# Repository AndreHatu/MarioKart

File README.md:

# Mario Kart with RC cars and ESP32s
This project aims at developing a real-life Mario Kart with RC cars and ESP32s.
The boards used utilize a single-core MCU (ESP-MINI-1 and ESP-SOLO-1). 
Schematics and wiring will be posted in the near future.

ECE477 Senior Design at Purdue University.

## How it works
We control RC cars with electronics replaced by our own ESP32. All communications are made using ESP-NOW, which is a Wi-Fi like wireless communication protocol. It enables low latency and long distance transmission of packets, with the only restriction they must be less than 250 bytes long.
Then, we place checkpoint towers and power-up blocks along the desired track and when cars run over them, a NFC tag is read and its information is sent to a central tower, which either updates records of checkpoints or determines what modifier to give the cars. Modifiers are randomly chosen using ESP's ```esp_random()``` function. Checkpoints are stored in two-dimensional arrays initialized upon race creation.

## Cloning
When cloning this repo, make sure to use ```git clone --recursive git@github.com:AndreHatu/MarioKart.git``` or run ```git submodule update --init --recursive``` after doing a standard clone. 
This ensures all dependencies are downloaded.

## Config, Build and Flash
To build, you will need to have installed Espressif's idf from their website.
Then run the following commands from a terminal.

```
idf.py set-target esp32
idf.py menuconfig
```
Inside the menuconfig, you might need to set the ```Components->freeRTOS->Run only on first core``` option in case your ESP32 only has one core (like the ones we are using for the project)
Then you can build and flash with
```
idf.py build
idf.py -p (PORT) flash
```

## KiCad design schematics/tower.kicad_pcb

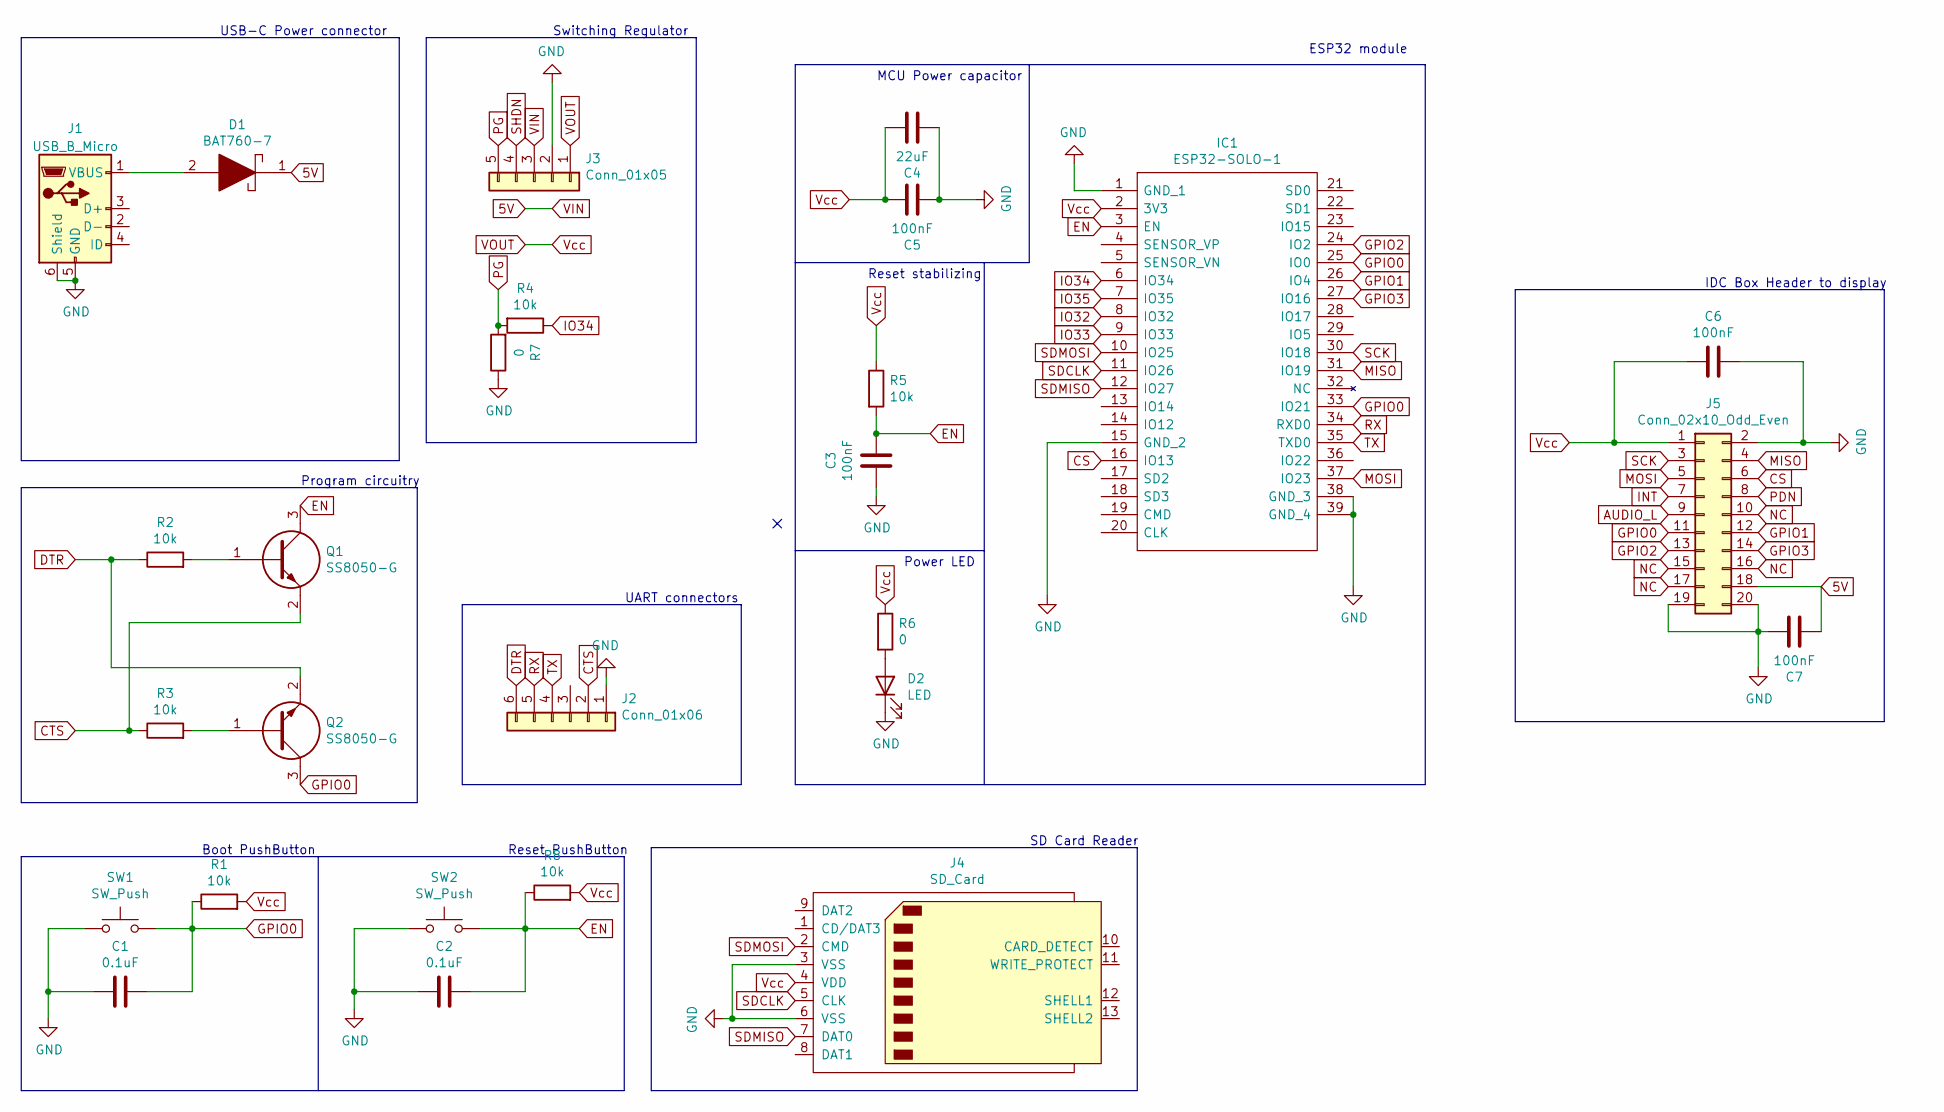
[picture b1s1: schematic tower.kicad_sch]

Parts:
C1, C2: 0.1uF; C_0805_2012Metric
C3, C5, C6, C7: 100nF; C_0805_2012Metric
C4: 22uF; C_0805_2012Metric
D1: BAT760-7; SOD2513X120N; Mouser Part Number 621-BAT760-7
D2: LED; APHCM2012QBCDF01
IC1: ESP32-SOLO-1; ESP32-WROOM-32; Manufacturer_Part_Number ESP32-SOLO-1; Mouser Part Number 356-ESP32-SOLO-1
J1: USB_B_Micro; USB_Micro-B_Molex-105017-0001
J2: Conn_01x06; PinSocket_1x06_P2.54mm_Vertical
J3: Conn_01x05; PinSocket_1x05_P2.54mm_Vertical
J4: SD_Card; SD_Kyocera_145638109211859+
J5: Conn_02x10_Odd_Even; PinSocket_2x10_P2.54mm_Vertical
Q1, Q2: SS8050-G; SOT95P240X115-3N; Mouser Part Number 750-SS8050-G
R1, R2, R3, R4, R5, R8: 10k; R_0805_2012Metric
R6, R7: 0; R_0805_2012Metric
SW1, SW2: SW_Push; SW_SPST_CK_KXT3

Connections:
5V: C7.2, D1.1, J3.3, J5.18
AUDIO_L: J5.9
CS: IC1.16 (IO13), J5.6
CTS: J2.2, Q1.2, R3.1
DTR: J2.6, Q2.2, R2.1
EN: C2.1, C3.1, IC1.3 (EN), Q1.3, R5.2, R8.1, SW2.2
GND: C1.2, C2.2, C3.2, C4.2, C5.2, C6.1, C7.1, D2.1 (K), IC1.1 (GND_1), IC1.15 (GND_2), IC1.38 (GND_3), IC1.39 (GND_4), J1.5 (GND), J1.6 (Shield), J2.1, J3.2, J4.3 (VSS), J4.6 (VSS), J5.2, J5.19, J5.20, R7.1, SW1.1, SW2.1
GPIO0: C1.1, IC1.25 (IO0), IC1.33 (IO21), J5.11, Q2.3, R1.1, SW1.2
GPIO1: IC1.26 (IO4), J5.12
GPIO2: IC1.24 (IO2), J5.13
GPIO3: IC1.27 (IO16), J5.14
INT: J5.7
IO32: IC1.8 (IO32)
IO33: IC1.9 (IO33)
IO34: IC1.6 (IO34), R4.1
IO35: IC1.7 (IO35)
MISO: IC1.31 (IO19), J5.4
MOSI: IC1.37 (IO23), J5.5
NC: J5.10, J5.15, J5.16, J5.17
unnamed: D2.2 (A), R6.2
unnamed: D1.2, J1.1 (VBUS)
unnamed: Q1.1, R2.2
unnamed: Q2.1, R3.2
PDN: J5.8
PG: J3.5, R4.2, R7.2
RX: IC1.34 (RXD0), J2.5
SCK: IC1.30 (IO18), J5.3
SDCLK: IC1.11 (IO26), J4.5 (CLK)
SDMISO: IC1.12 (IO27), J4.7 (DAT0)
SDMOSI: IC1.10 (IO25), J4.2 (CMD)
SHDN: J3.4
TX: IC1.35 (TXD0), J2.4
VOUT: C4.1, C5.1, C6.2, IC1.2 (3V3), J3.1, J4.4 (VDD), J5.1, R1.2, R5.1, R6.1, R8.2

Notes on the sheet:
Program circuitry
ESP32 module
IDC Box Header to display
Reset PushButton
Switching Regulator
SD Card Reader
Reset stabilizing
USB-C Power connector
UART connectors
Power LED
MCU Power capacitor
Boot PushButton

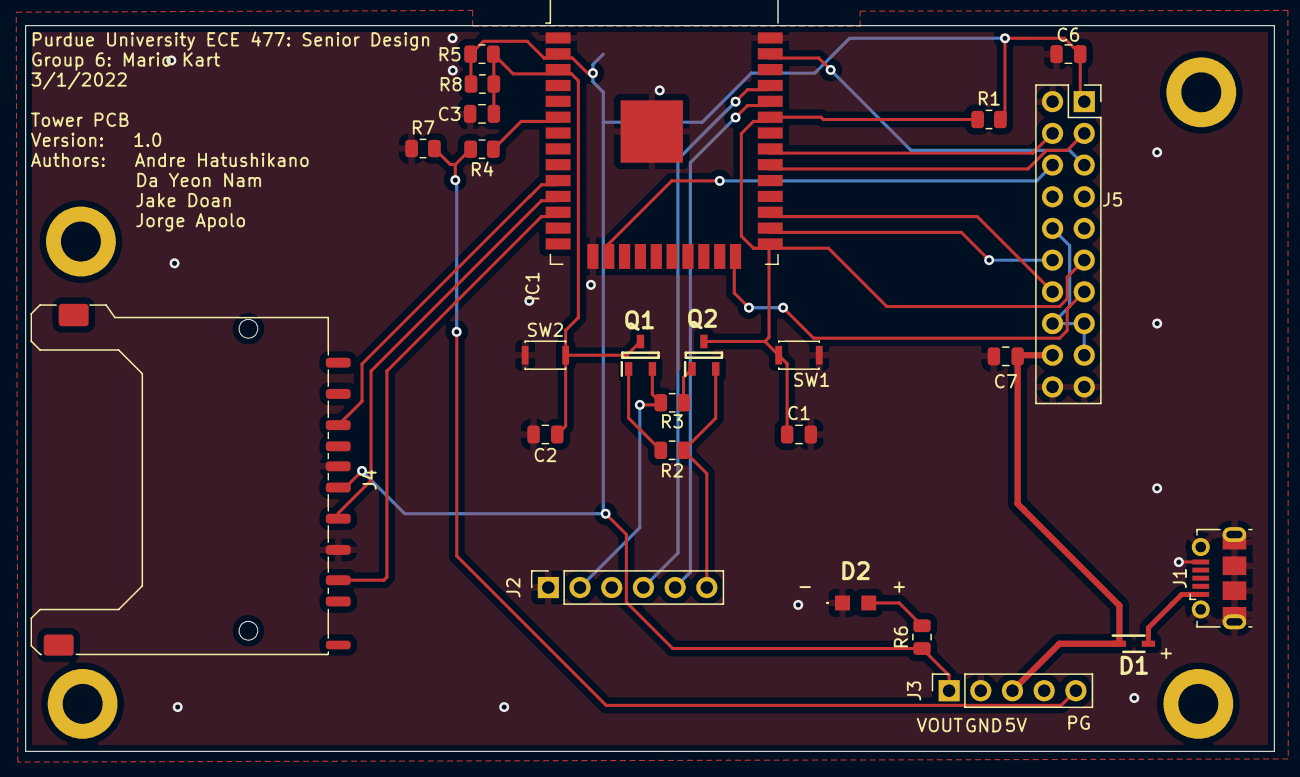
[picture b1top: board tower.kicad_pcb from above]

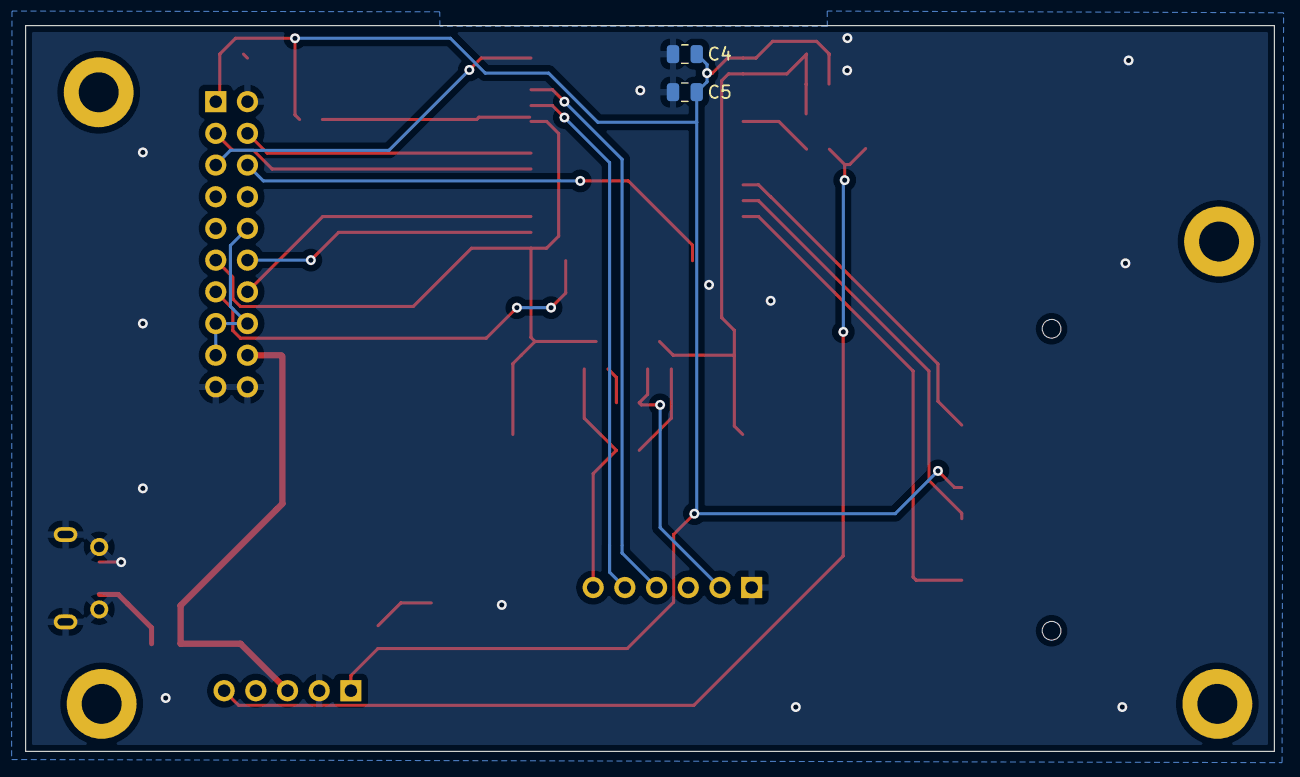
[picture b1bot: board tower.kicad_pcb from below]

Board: 2 copper layers, 100.1 x 58.2 mm, 27 parts (2 on the bottom side), 26 nets.

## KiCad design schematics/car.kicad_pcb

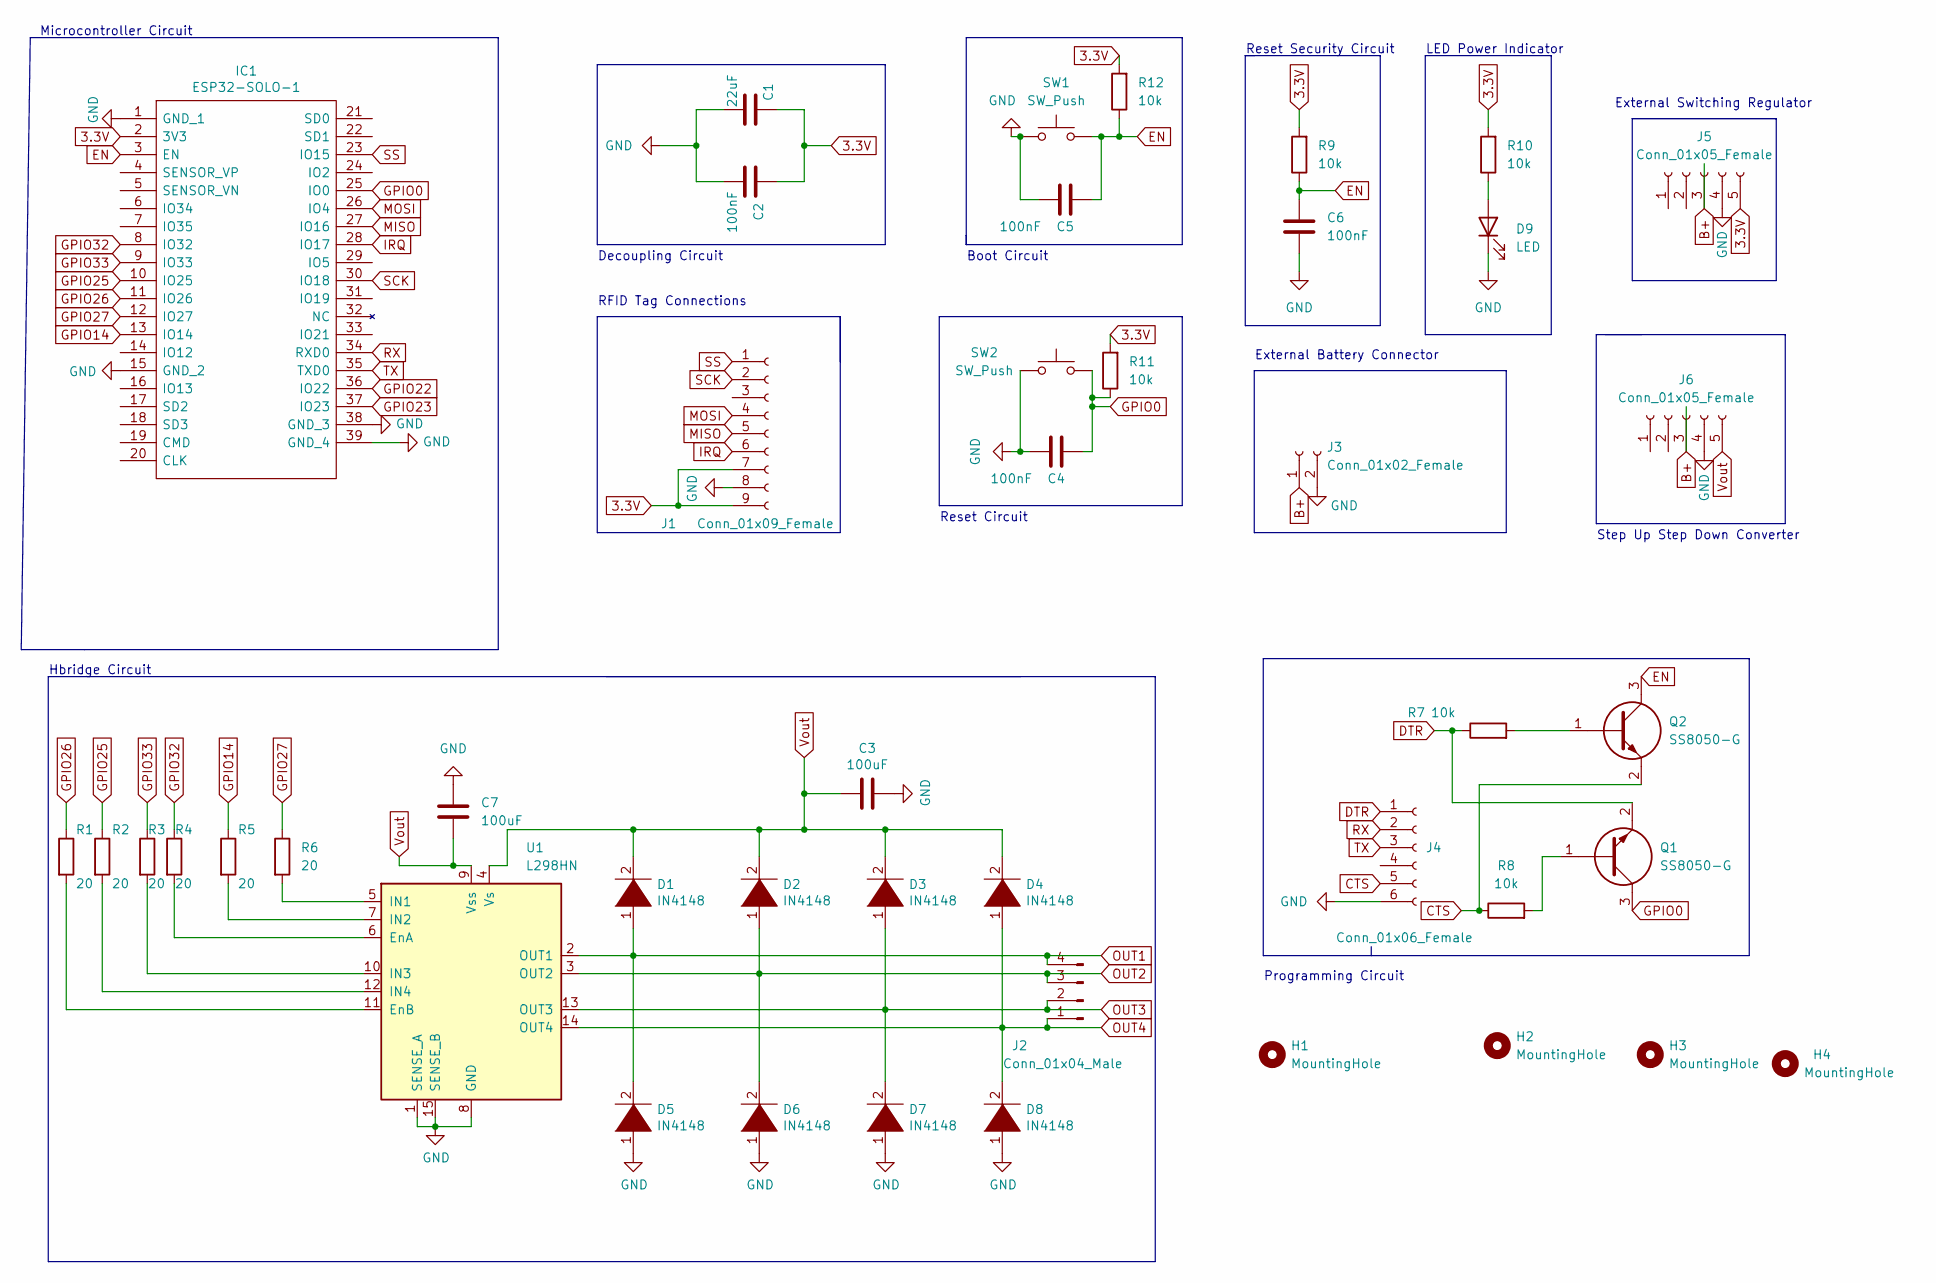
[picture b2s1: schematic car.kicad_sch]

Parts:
C1: 22uF; C_0805_2012Metric
C2, C4, C5, C6: 100nF; C_0805_2012Metric
C3, C7: 100uF; CP_Radial_D8.0mm_P5.00mm
D1, D2, D3, D4, D5, D6, D7, D8: IN4148; D_SOD-123F
D9: LED; APHCM2012QBCDF01
H1, H2, H3, H4: MountingHole; MountingHole_2.5mm_Pad
IC1: ESP32-SOLO-1; ESP32-SOLO-ONE; Manufacturer_Part_Number ESP32-SOLO-1; Mouser Part Number 356-ESP32-SOLO-1
J1: Conn_01x09_Female; PinHeader_1x09_P2.54mm_Vertical
J2: Conn_01x04_Male; PinHeader_1x04_P2.54mm_Vertical
J3: Conn_01x02_Female; PinHeader_1x02_P2.54mm_Vertical
J4: Conn_01x06_Female; PinHeader_1x06_P2.54mm_Vertical
J5, J6: Conn_01x05_Female; PinHeader_1x05_P2.54mm_Vertical
Q1, Q2: SS8050-G; SOT95P240X115-3N; Mouser Part Number 750-SS8050-G
R1, R2, R3, R4, R5, R6: 20; R_0805_2012Metric
R7, R8, R9, R10, R11, R12: 10k; R_0805_2012Metric
SW1, SW2: SW_Push; SW_SPST_CK_KXT3
U1: L298HN; TO-220-15_P2.54x2.54mm_StaggerOdd_Lead4.58mm_Vertical

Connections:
3.3V: C1.1, C2.1, IC1.2 (3V3), J1.7, J1.9, J5.5, R9.2, R10.2, R11.2, R12.2
B+: J3.1, J5.3, J6.3
CTS: J4.5, Q2.2, R8.1
DTR: J4.1, Q1.2, R7.1
EN: C5.2, C6.1, IC1.3 (EN), Q2.3, R9.1, R12.1, SW1.2
GND: C1.2, C2.2, C3.1, C4.1, C5.1, C6.2, C7.1, D5.1 (K), D6.1 (K), D7.1 (K), D8.1 (K), D9.1 (K), IC1.1 (GND_1), IC1.15 (GND_2), IC1.38 (GND_3), IC1.39 (GND_4), J1.8, J3.2, J4.6, J5.4, J6.4, SW1.1, SW2.1, U1.1 (SENSE_A), U1.8 (GND), U1.15 (SENSE_B)
GPIO0: C4.2, IC1.25 (IO0), Q1.3, R11.1, SW2.2
GPIO14: IC1.13 (IO14), R5.1
GPIO22: IC1.36 (IO22)
GPIO23: IC1.37 (IO23)
GPIO25: IC1.10 (IO25), R2.1
GPIO26: IC1.11 (IO26), R1.1
GPIO27: IC1.12 (IO27), R6.1
GPIO32: IC1.8 (IO32), R4.1
GPIO33: IC1.9 (IO33), R3.1
IRQ: IC1.28 (IO17), J1.6
MISO: IC1.27 (IO16), J1.5
MOSI: IC1.26 (IO4), J1.4
unnamed: D9.2 (A), R10.1
unnamed: Q1.1, R8.2
unnamed: Q2.1, R7.2
unnamed: R1.2, U1.11 (EnB)
unnamed: R2.2, U1.12 (IN4)
unnamed: R3.2, U1.10 (IN3)
unnamed: R4.2, U1.6 (EnA)
unnamed: R5.2, U1.7 (IN2)
unnamed: R6.2, U1.5 (IN1)
OUT1: D1.1 (K), D5.2 (A), J2.4, U1.2 (OUT1)
OUT2: D2.1 (K), D6.2 (A), J2.3, U1.3 (OUT2)
OUT3: D3.1 (K), D7.2 (A), J2.2, U1.13 (OUT3)
OUT4: D4.1 (K), D8.2 (A), J2.1, U1.14 (OUT4)
RX: IC1.34 (RXD0), J4.2
SCK: IC1.30 (IO18), J1.2
SS: IC1.23 (IO15), J1.1
TX: IC1.35 (TXD0), J4.3
Vout: C3.2, C7.2, D1.2 (A), D2.2 (A), D3.2 (A), D4.2 (A), J6.5, U1.4 (Vs), U1.9 (Vss)

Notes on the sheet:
Step Up Step Down Converter
Boot Circuit
Microcontroller Circuit
Programming Circuit
External Switching Regulator
External Battery Connector
Hbridge Circuit
Decoupling Circuit
RFID Tag Connections
Reset Circuit
Reset Security Circuit
LED Power Indicator

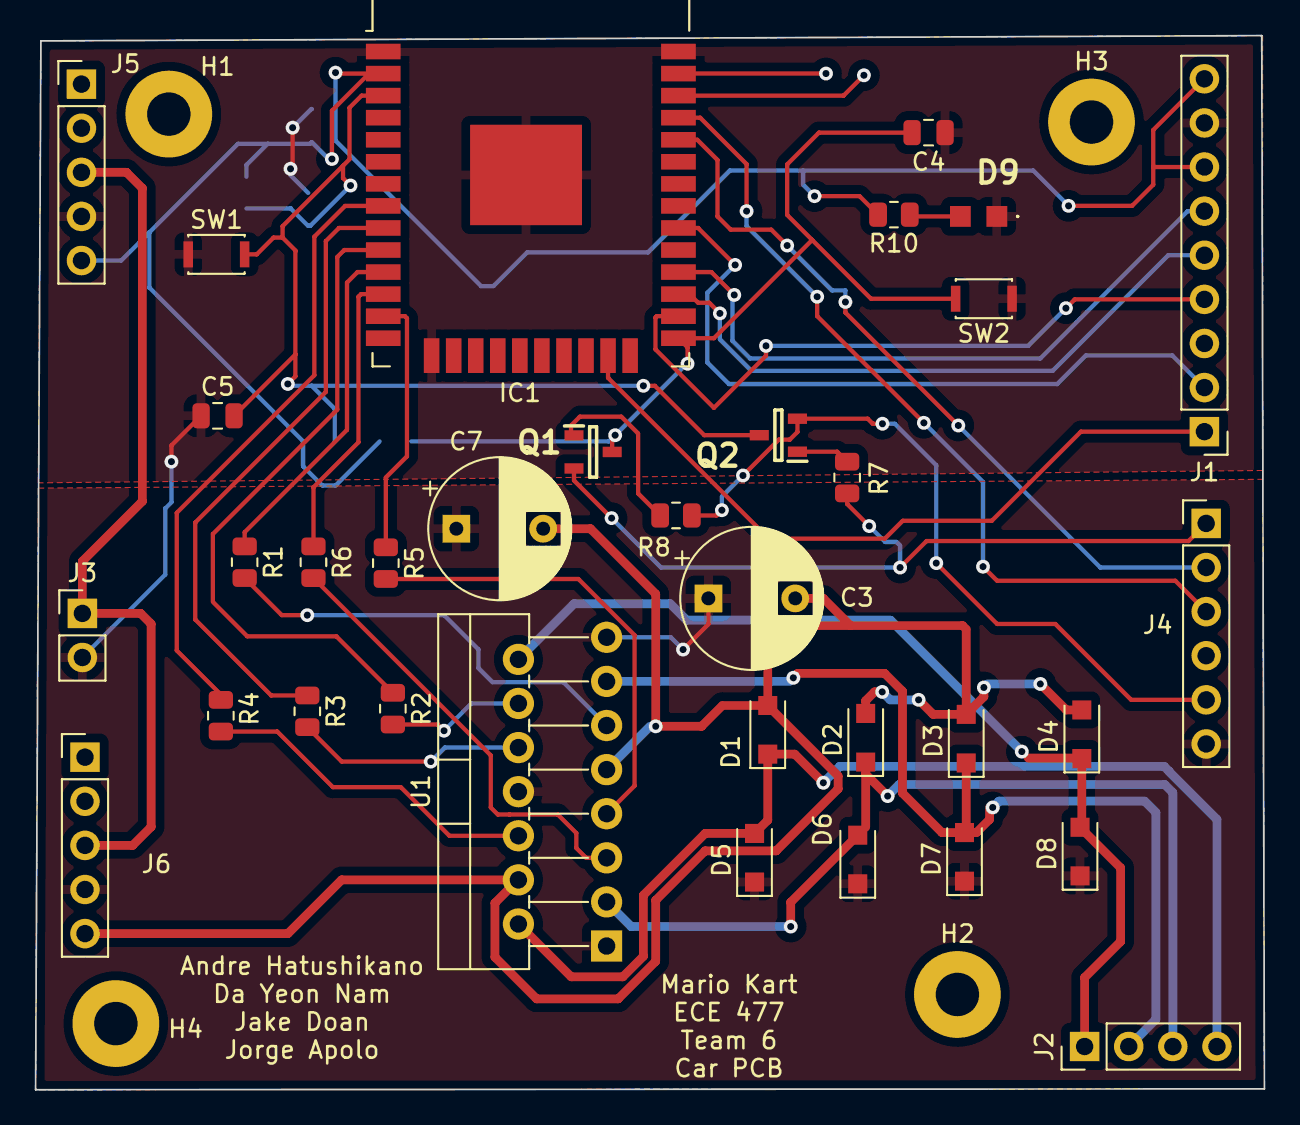
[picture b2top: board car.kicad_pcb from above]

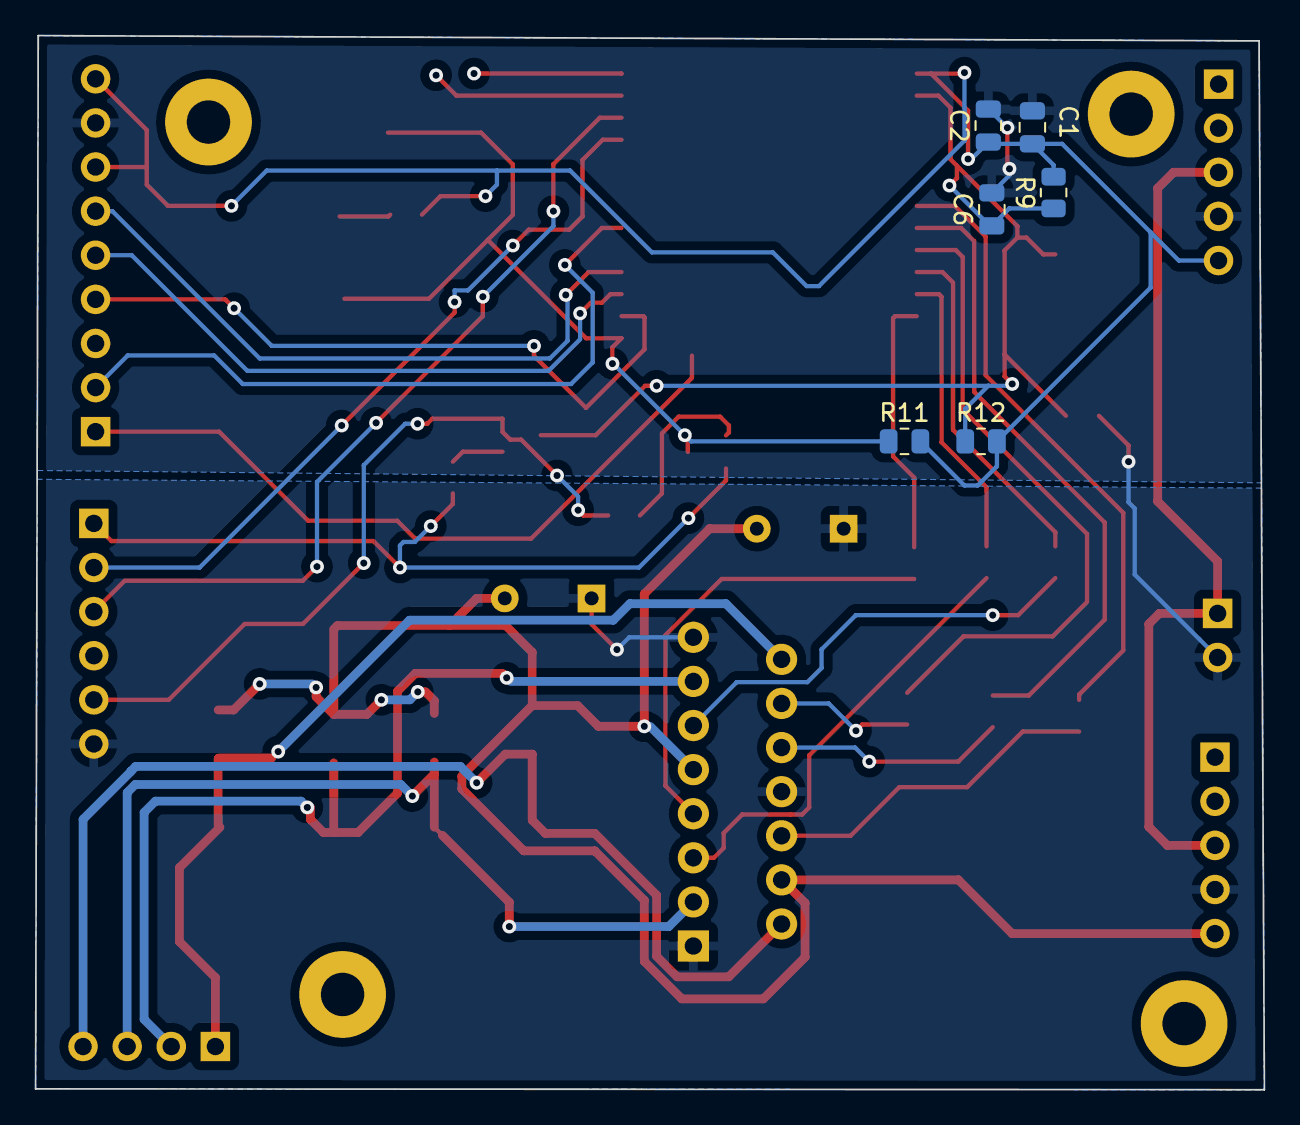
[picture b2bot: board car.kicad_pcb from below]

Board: 2 copper layers, 70.8 x 60.7 mm, 44 parts (6 on the bottom side), 34 nets.

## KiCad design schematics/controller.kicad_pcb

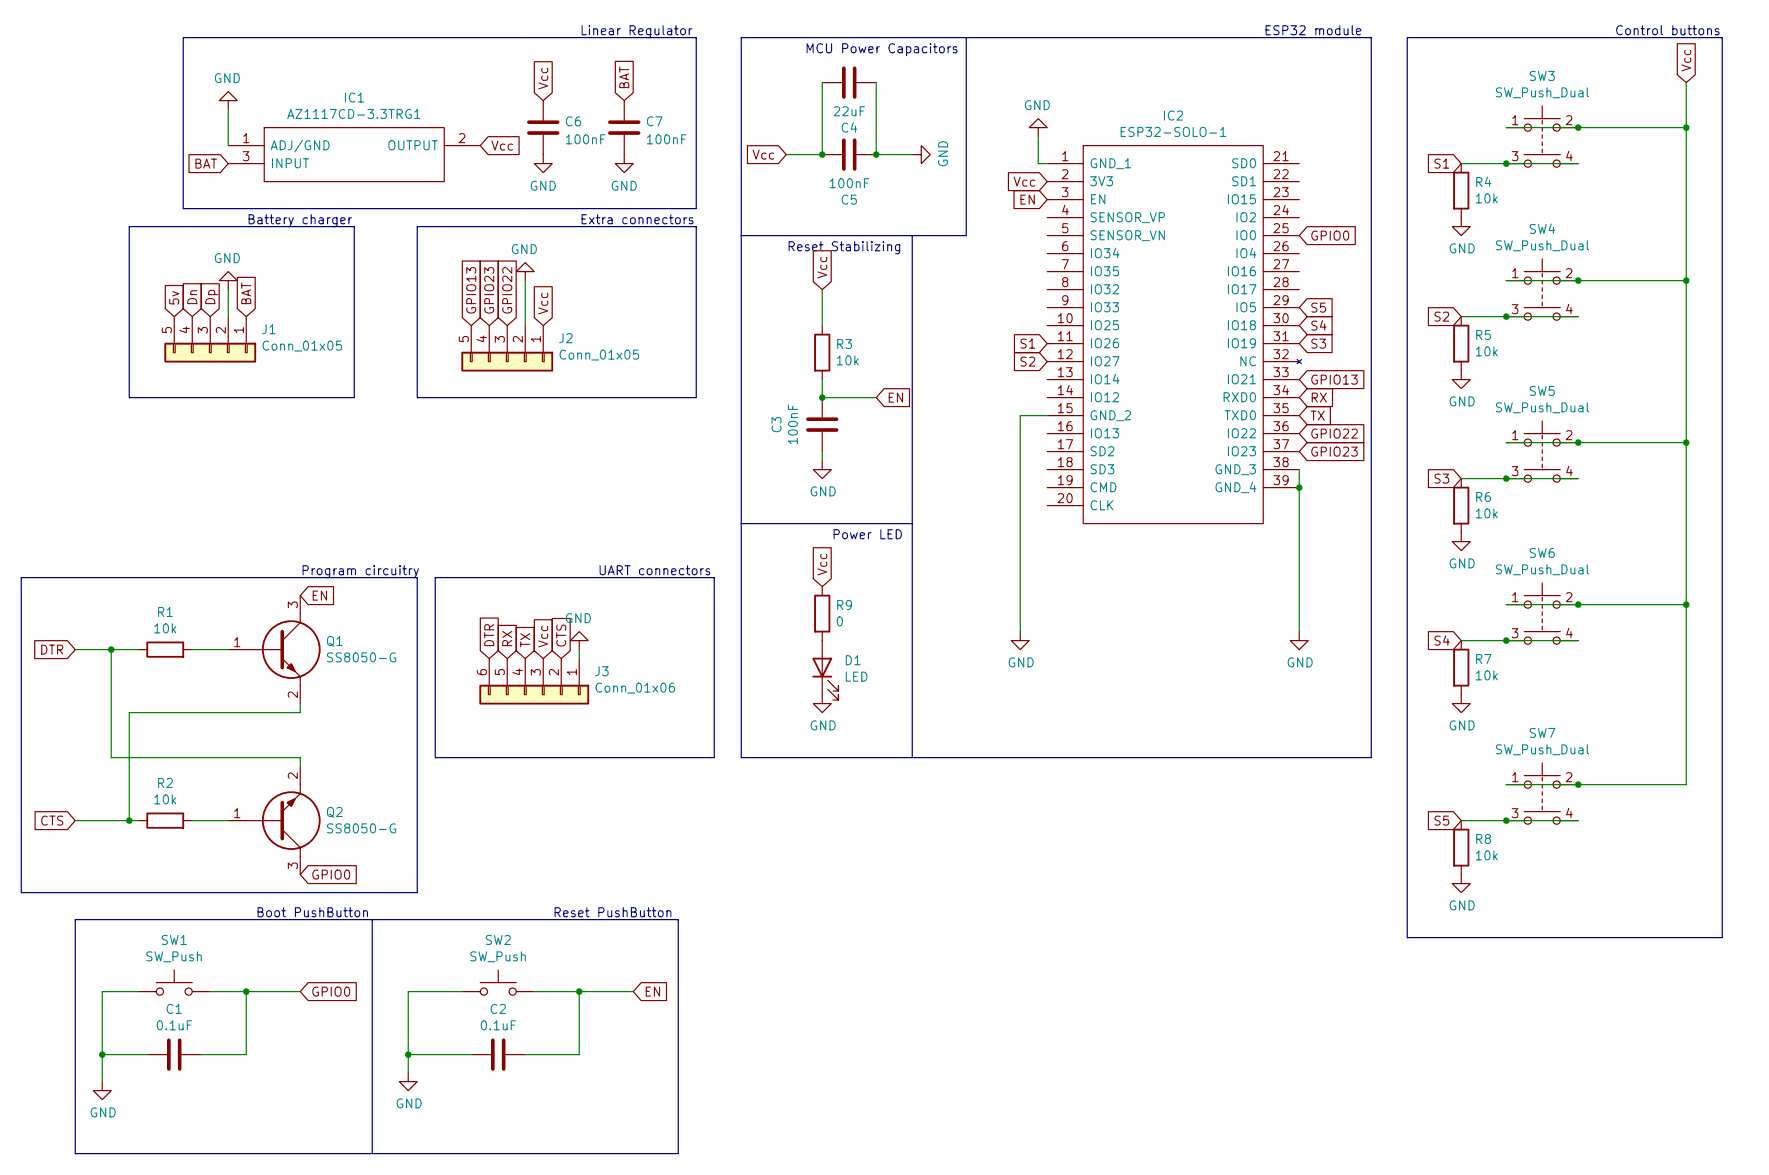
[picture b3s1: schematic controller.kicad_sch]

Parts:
C1, C2: 0.1uF; C_0805_2012Metric
C3, C5, C6, C7: 100nF; C_0805_2012Metric
C4: 22uF; C_0805_2012Metric
D1: LED; APHCM2012QBCDF01
IC1: AZ1117CD-3.3TRG1; AZ1117CD33TRG1; Mouser Part Number 621-AZ1117CD-3.3TRG1
IC2: ESP32-SOLO-1; ESP32SOLO1; Manufacturer_Part_Number ESP32-SOLO-1; Mouser Part Number 356-ESP32-SOLO-1
J1, J2: Conn_01x05; PinSocket_1x05_P2.54mm_Vertical
J3: Conn_01x06; PinSocket_1x06_P2.54mm_Vertical
Q1, Q2: SS8050-G; SOT95P240X115-3N; Mouser Part Number 750-SS8050-G
R1, R2, R3, R4, R5, R6, R7, R8: 10k; R_0805_2012Metric
R9: 0; R_0805_2012Metric
SW1, SW2: SW_Push; SW_SPST_CK_KXT3
SW3, SW4, SW5, SW6, SW7: SW_Push_Dual; SW_TH_Tactile_Omron_B3F-10xx

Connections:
5v: J1.5
BAT: C7.1, IC1.3 (INPUT), J1.1
CTS: J3.2, Q1.2, R2.1
DTR: J3.6, Q2.2, R1.1
Dn: J1.4
Dp: J1.3
EN: C2.1, C3.1, IC2.3 (EN), Q1.3, R3.2, SW2.2; also elsewhere on the board
GND: C1.2, C2.2, C3.2, C4.2, C5.2, C6.2, C7.2, D1.1 (K), IC1.1 (ADJ/GND), IC2.1 (GND_1), IC2.15 (GND_2), IC2.38 (GND_3), IC2.39 (GND_4), J1.2, J2.2, J3.1, R4.2, R5.2, R6.2, R7.2, R8.2, SW1.1, SW2.1
GPIO0: C1.1, IC2.25 (IO0), Q2.3, SW1.2; also elsewhere on the board
GPIO13: IC2.33 (IO21), J2.5
GPIO22: IC2.36 (IO22), J2.3
GPIO23: IC2.37 (IO23), J2.4
unnamed: D1.2 (A), R9.2
unnamed: Q1.1, R1.2
unnamed: Q2.1, R2.2
RX: IC2.34 (RXD0), J3.5
S1: IC2.11 (IO26), R4.1, SW3.3, SW3.4
S2: IC2.12 (IO27), R5.1, SW4.3, SW4.4
S3: IC2.31 (IO19), R6.1, SW5.3, SW5.4
S4: IC2.30 (IO18), R7.1, SW6.3, SW6.4
S5: IC2.29 (IO5), R8.1, SW7.3, SW7.4
TX: IC2.35 (TXD0), J3.4
Vcc: C4.1, C5.1, C6.1, IC1.2 (OUTPUT), IC2.2 (3V3), J2.1, J3.3, R3.1, R9.1, SW3.1, SW3.2, SW4.1, SW4.2, SW5.1, SW5.2, SW6.1, SW6.2, SW7.1, SW7.2; also elsewhere on the board

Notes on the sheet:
Boot PushButton
MCU Power Capacitors
Control buttons
Linear Regulator
Extra connectors
UART connectors
Program circuitry
Reset Stabilizing
Power LED
ESP32 module
Reset PushButton
Battery charger

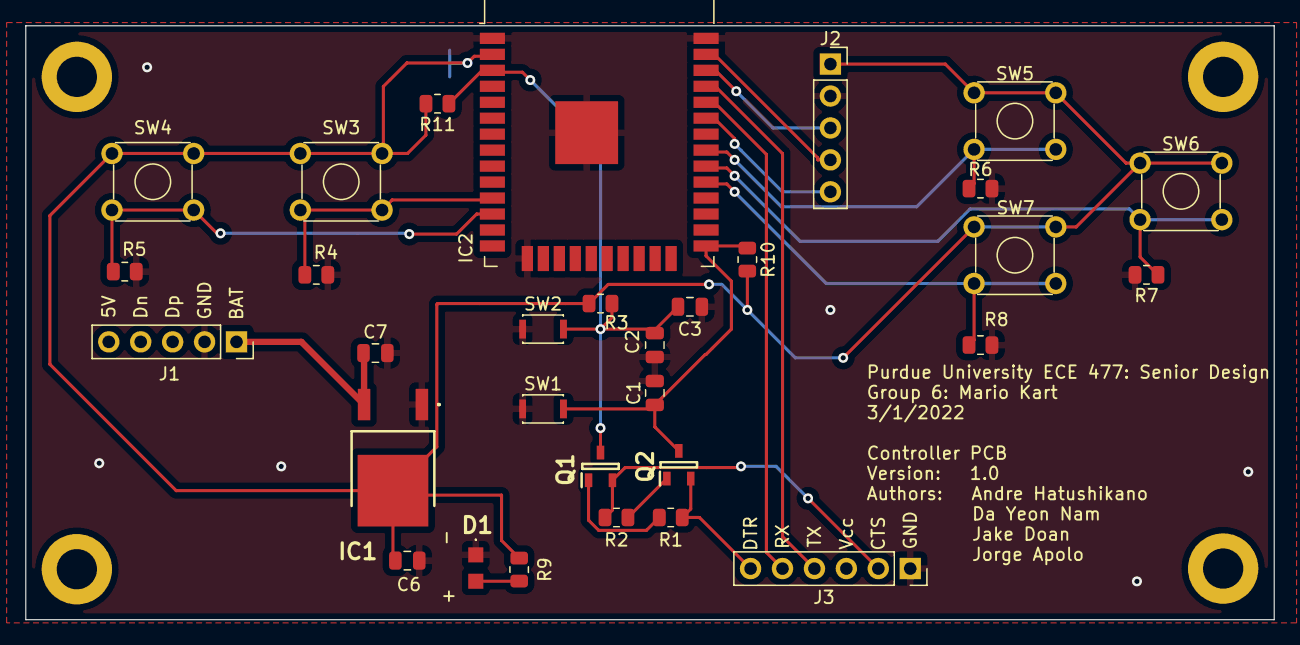
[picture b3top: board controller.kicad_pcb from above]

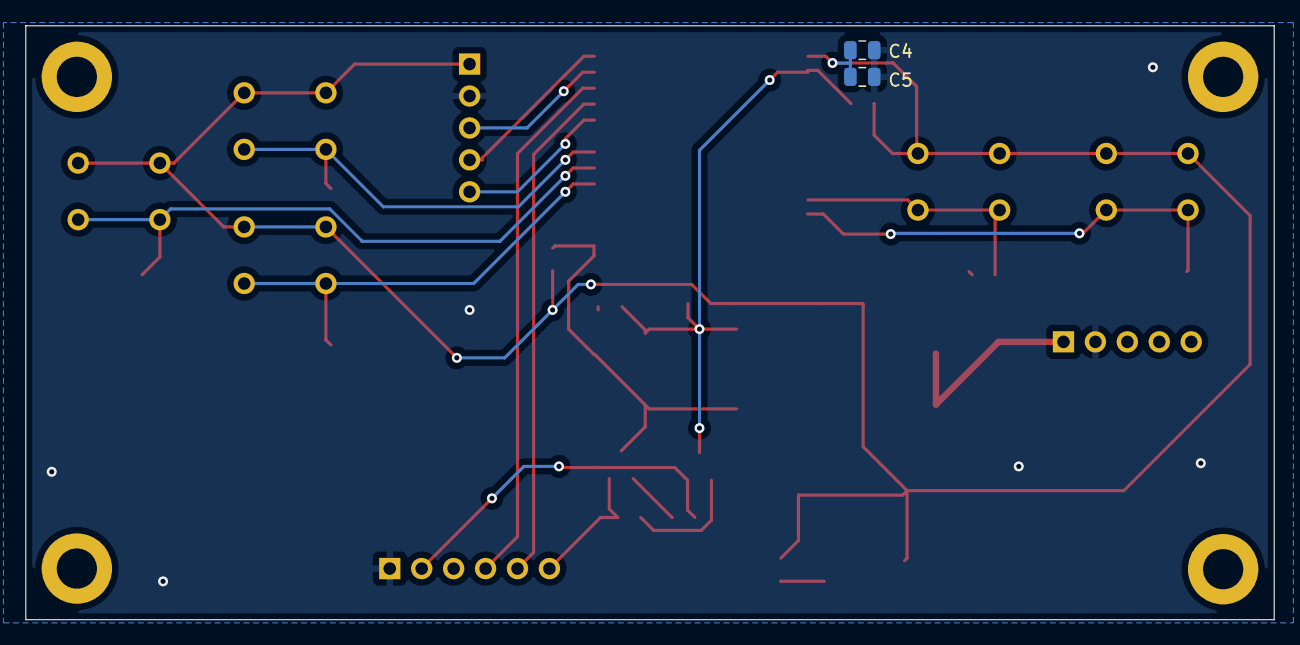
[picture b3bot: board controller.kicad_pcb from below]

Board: 2 copper layers, 99.3 x 47.2 mm, 33 parts (2 on the bottom side), 20 nets.

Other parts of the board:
R10, R11: 10k; R_0805_2012Metric

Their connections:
EN: R11.1; also elsewhere on the board
GPIO0: R10.1; also elsewhere on the board
Vcc: R10.2, R11.2; also elsewhere on the board

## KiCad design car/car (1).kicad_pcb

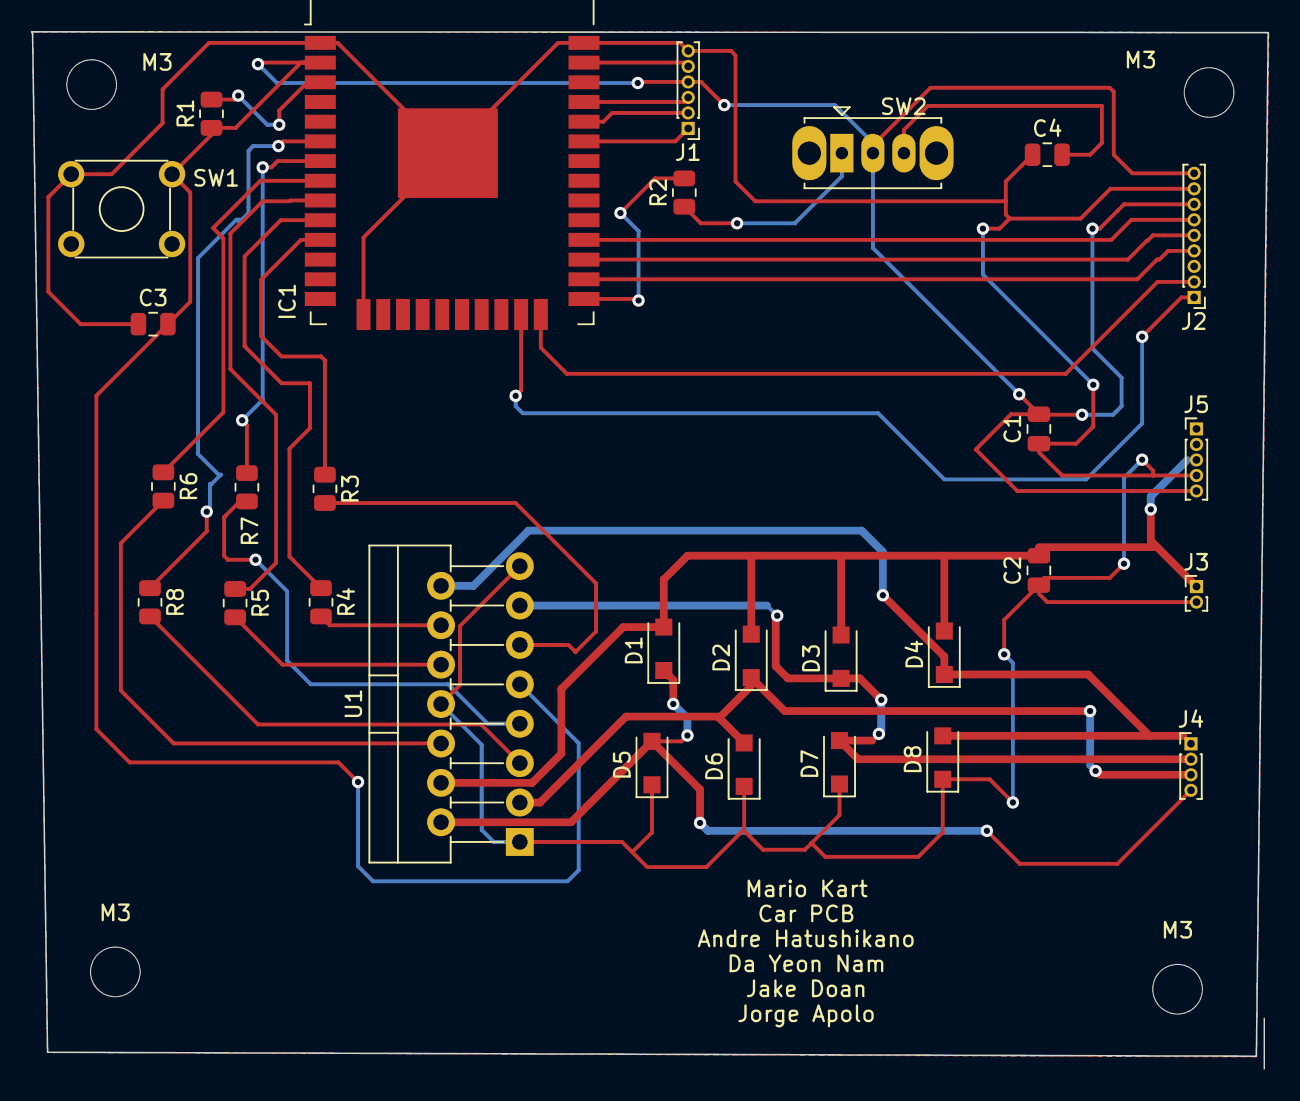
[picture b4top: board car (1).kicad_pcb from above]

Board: 2 copper layers, 79.7 x 66.9 mm, 33 parts (0 on the bottom side), 24 nets.

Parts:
C1, C2: 100nF; C_0805_2012Metric
C3, C4: 100uF; C_0805_2012Metric
D1, D2, D3, D4, D5, D6, D7, D8: IN4148; D_SOD-123F
IC1: ESP32-SOLO-1; ESP32-SOLO-ONE
J1: Conn_01x06_Female; PinHeader_1x06_P1.00mm_Vertical
J2: Conn_01x09_Female; PinHeader_1x09_P1.00mm_Vertical
J3: Conn_01x02_Female; PinHeader_1x02_P1.00mm_Vertical
J4: Conn_01x04_Male; PinHeader_1x04_P1.00mm_Vertical
J5: Conn_01x05_Female; PinHeader_1x05_P1.00mm_Vertical
M3, M3#2, M3#3, M3#4: MountingHole_3.2mm_M3_DIN965
R1, R2: 10k; R_0805_2012Metric
R3, R4, R5, R6, R7, R8: 20; R_0805_2012Metric
SW1: SW_Push; SW_TH_Tactile_Omron_B3F-10xx
SW2: SW_SPDT; SW_Slide_1P2T_CK_OS102011MS2Q
U1: L298HN; TO-220-15_P2.54x2.54mm_StaggerOdd_Lead4.58mm_Vertical

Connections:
+3V3: C1.2, C3.2, IC1.2 (3V3), J1.4, J2.7, J2.9, J5.5, R1.1, SW1.2, SW2.2 (B), U1.9 (Vss)
+9V: C2.2, D1.2 (A), D2.2 (A), D3.2 (A), D4.2 (A), J3.1, J5.3, U1.4 (Vs)
GND: C1.1, C2.1, C3.1, C4.1, D5.1 (K), D6.1 (K), D7.1 (K), D8.1 (K), IC1.1 (GND_1), IC1.15 (GND_2), IC1.38 (GND_3), IC1.39 (GND_4), J1.6, J2.8, J3.2, J5.4, SW1.1, U1.1 (SENSE_A), U1.8 (GND), U1.15 (SENSE_B)
unnamed: C4.2, SW2.3 (C)
unnamed: IC1.3 (EN), R1.2
unnamed: IC1.8 (IO32), R6.1
unnamed: IC1.9 (IO33), R5.1
unnamed: IC1.10 (IO25), R4.1
unnamed: IC1.11 (IO26), R3.1
unnamed: IC1.12 (IO27), R8.1
unnamed: IC1.13 (IO14), R7.1
unnamed: IC1.23 (IO15), J2.1
unnamed: IC1.24 (IO2), J2.2
unnamed: IC1.25 (IO0), R2.2
unnamed: IC1.26 (IO4), J2.4
unnamed: IC1.27 (IO16), J2.5
unnamed: IC1.28 (IO17), J2.6
unnamed: IC1.34 (RXD0), J1.2
unnamed: IC1.35 (TXD0), J1.3
unnamed: R2.1, SW2.1 (A)
OUT1: D1.1 (K), D5.2 (A), J4.4, U1.2 (OUT1)
OUT2: D2.1 (K), D6.2 (A), J4.3, U1.3 (OUT2)
OUT3: D3.1 (K), D7.2 (A), J4.2, U1.13 (OUT3)
OUT4: D4.1 (K), D8.2 (A), J4.1, U1.14 (OUT4)

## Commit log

2022-01-29 some rc522 stuff
2022-01-29 editing readme
2022-01-30 some gpio reading
2022-01-31 new espnow example
2022-01-31 failing to transmit data
2022-01-31 updated gitignore
2022-01-31 added shared structures file
2022-01-31 correct file extension
2022-01-31 it works!
2022-01-31 config/car to tower
2022-01-31 config/car to tower 2
2022-01-31 updated config file
2022-02-01 maybe now not adding build?
2022-02-04 Tower code in process
2022-02-04 added packet attr
2022-02-04 cleanup and made it compile
2022-02-04 added new esp32s
2022-02-04 a lot of cleanup
2022-02-04 (very) basic tag handling in tower
2022-02-04 communication between car and tower working
2022-02-05 uncommented RC522 module
2022-02-06 Controller works with car
2022-02-06 adding spi_practice
2022-02-06 cleanup
2022-02-06 fixed memory leaks
2022-02-06 gitsubmodules
2022-02-07 random gen + tag handler
2022-02-10 hashmap added
2022-02-11 adding pwm.c module
2022-02-12 fixed rc522 submodule
2022-02-13 controller schematics
2022-02-16 checkpoint and modifier
2022-02-16 peer connection btw two cars
2022-02-16 update PWM
2022-02-16 Car schematics
    schematics for the car with the motor control L298
2022-02-16 minor change
2022-02-18 updated controller schematic
2022-02-19 merge
2022-02-19 update all power for 1 car
2022-02-23 test
2022-02-23 adding fn
2022-02-23 car connection
2022-02-23 activate modifier packet
2022-02-23 added drivers for display
2022-02-24 some example code
2022-02-28 tower pcb
2022-02-28 Car schematics
    car schematics almost finished
2022-03-03 finished (I think) schematics for tower and controller
2022-03-03 car presentation
    is done for now...
2022-03-03 car updated hopefully works
    temp file to see if error
2022-03-03 with makelist
    make list
2022-03-03 new folder
    new folder
2022-03-03 converted all schematics into kicad6 format
2022-03-09 think Ive finished the schematics
2022-03-09 display init commit
2022-03-09 2 cars communicate
2022-03-09 Global variable of mac addresses for car 1 and car 2
2022-03-09 debounce
2022-03-09 update controller
2022-03-10 final pcbs and schematics
2022-03-23 some tower stuff
2022-03-30 updated pins for controller
2022-04-06 update new MAC
2022-04-06 display menu
2022-04-09 getting glitch for race display screen
2022-04-09 tag values
2022-04-09 race display
2022-04-09 going back to menu and start new game
2022-04-10 update car
2022-04-10 new car
2022-04-13 update tower
2022-04-13 display data
2022-04-13 calculate lap time & display
2022-04-13 update car2
2022-04-16 refactored some of the race code
2022-04-21 display lap statistics
2022-04-22 display race statistics
2022-04-23 make car send packet back to tower when using modifier, tower now displays modifier
2022-04-23 lil fix
2022-04-23 display modified
2022-04-24 display modification
2022-04-24 display modificiation + car2 code update
2022-04-25 finalize display
2022-04-26 display modifier on car 1
2022-04-27 re-prioritized tasks
2022-04-27 update tag
2022-04-27 init implementation
2022-04-28 arrays seem to be working...
